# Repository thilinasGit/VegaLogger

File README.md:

# VegaLogger
This repo contains files that is used in telemetery data logger originally used in Vega ETX.

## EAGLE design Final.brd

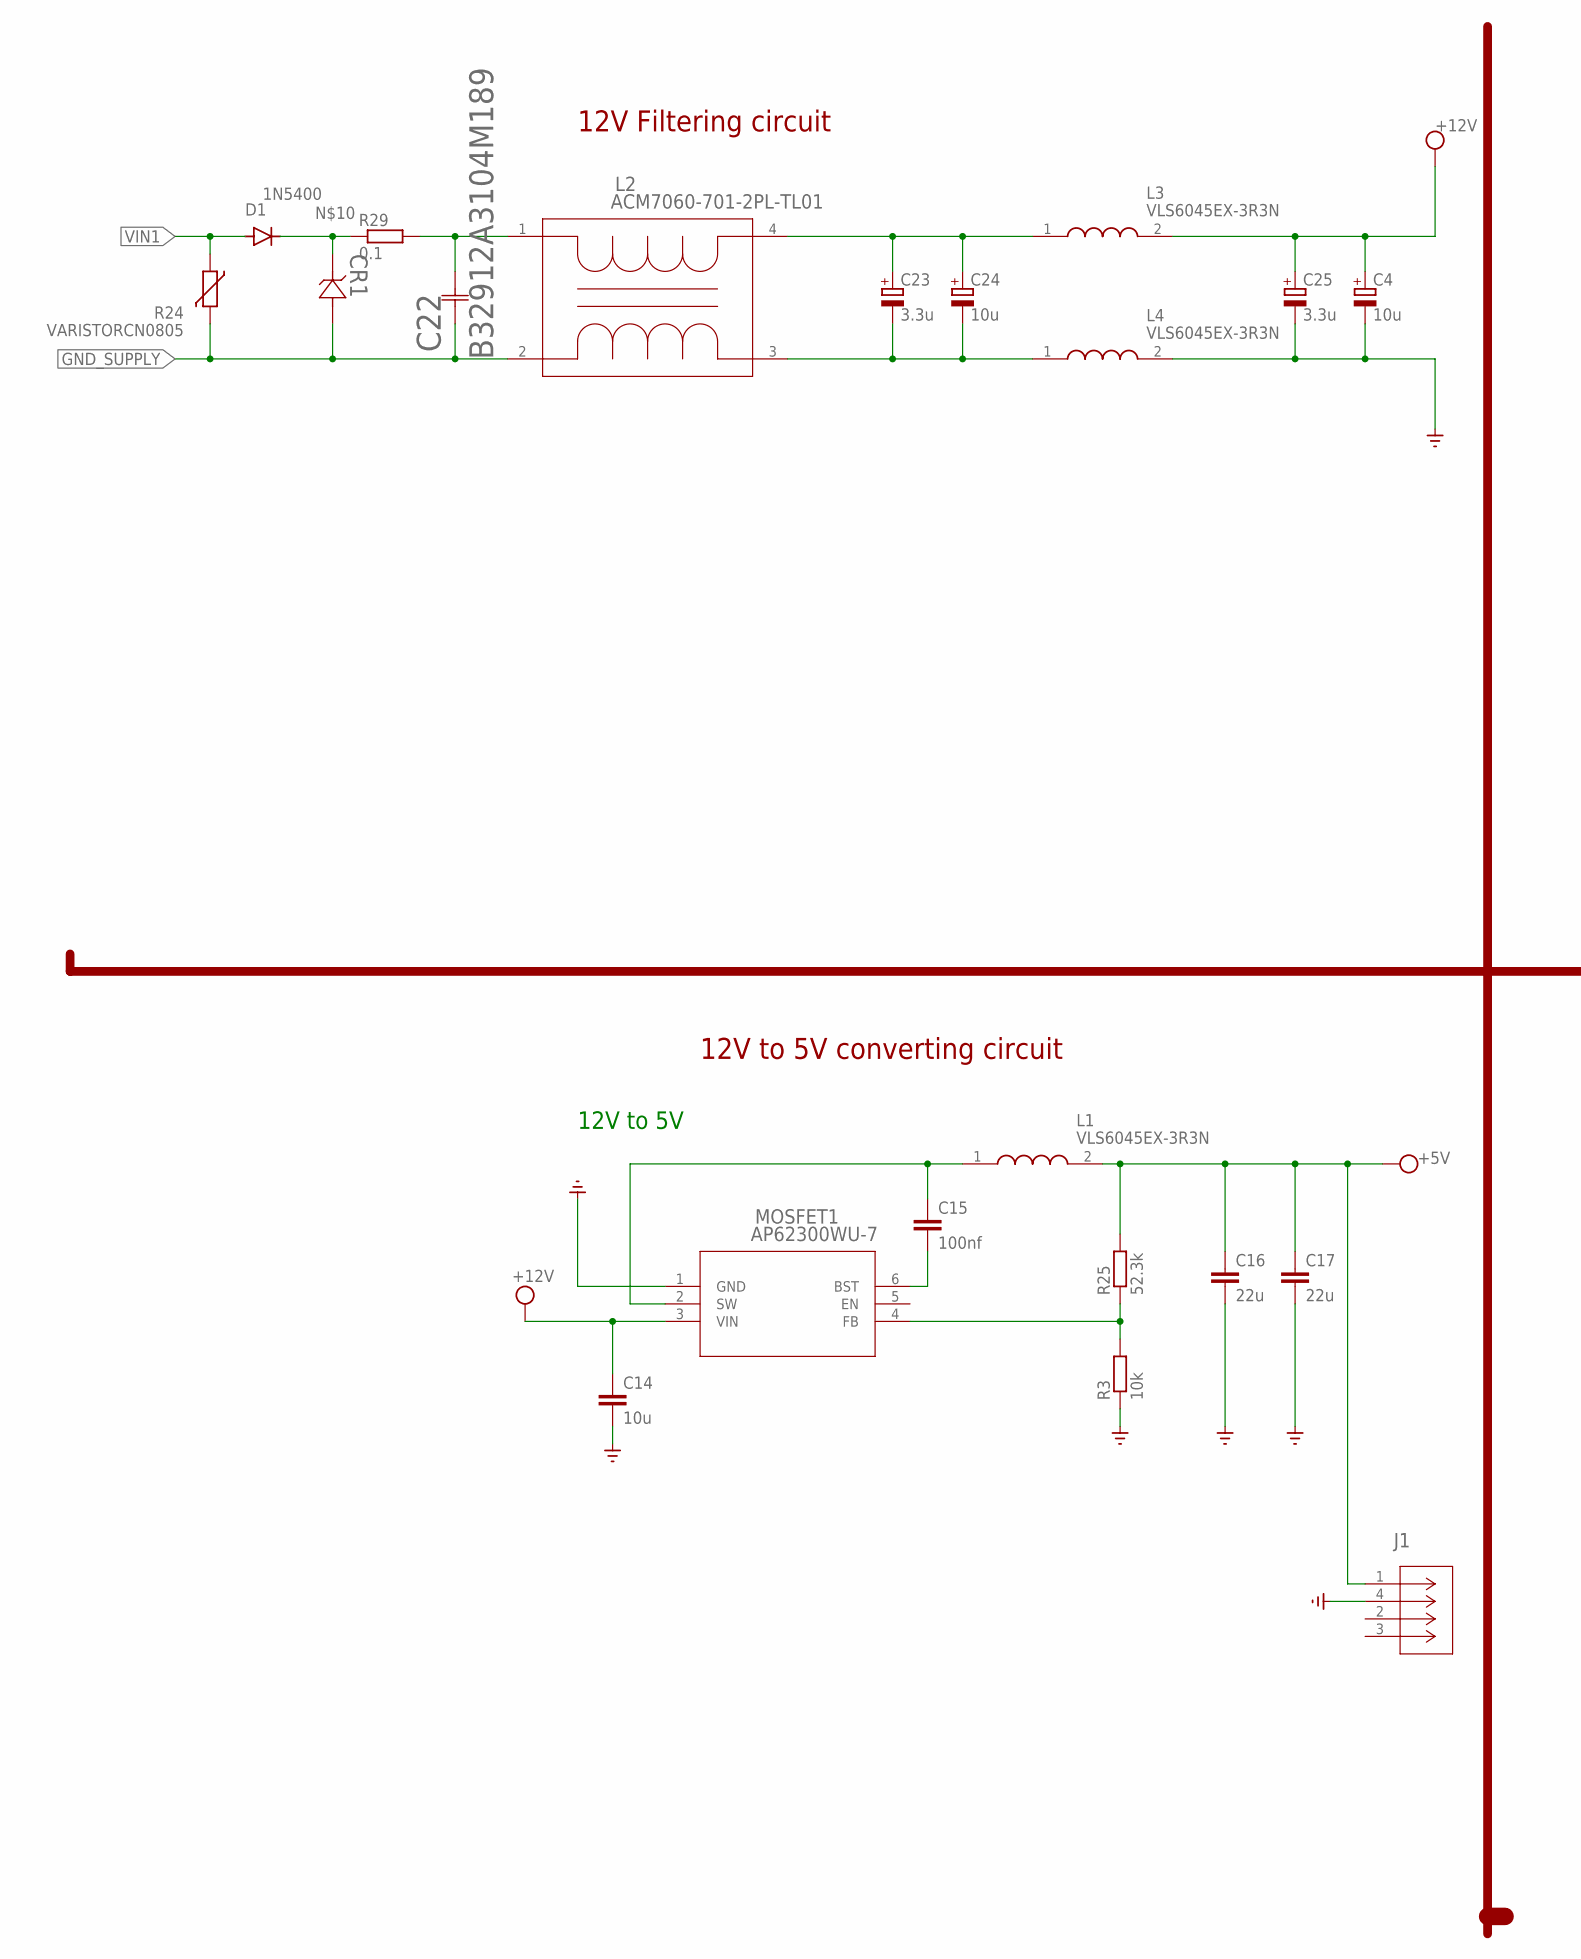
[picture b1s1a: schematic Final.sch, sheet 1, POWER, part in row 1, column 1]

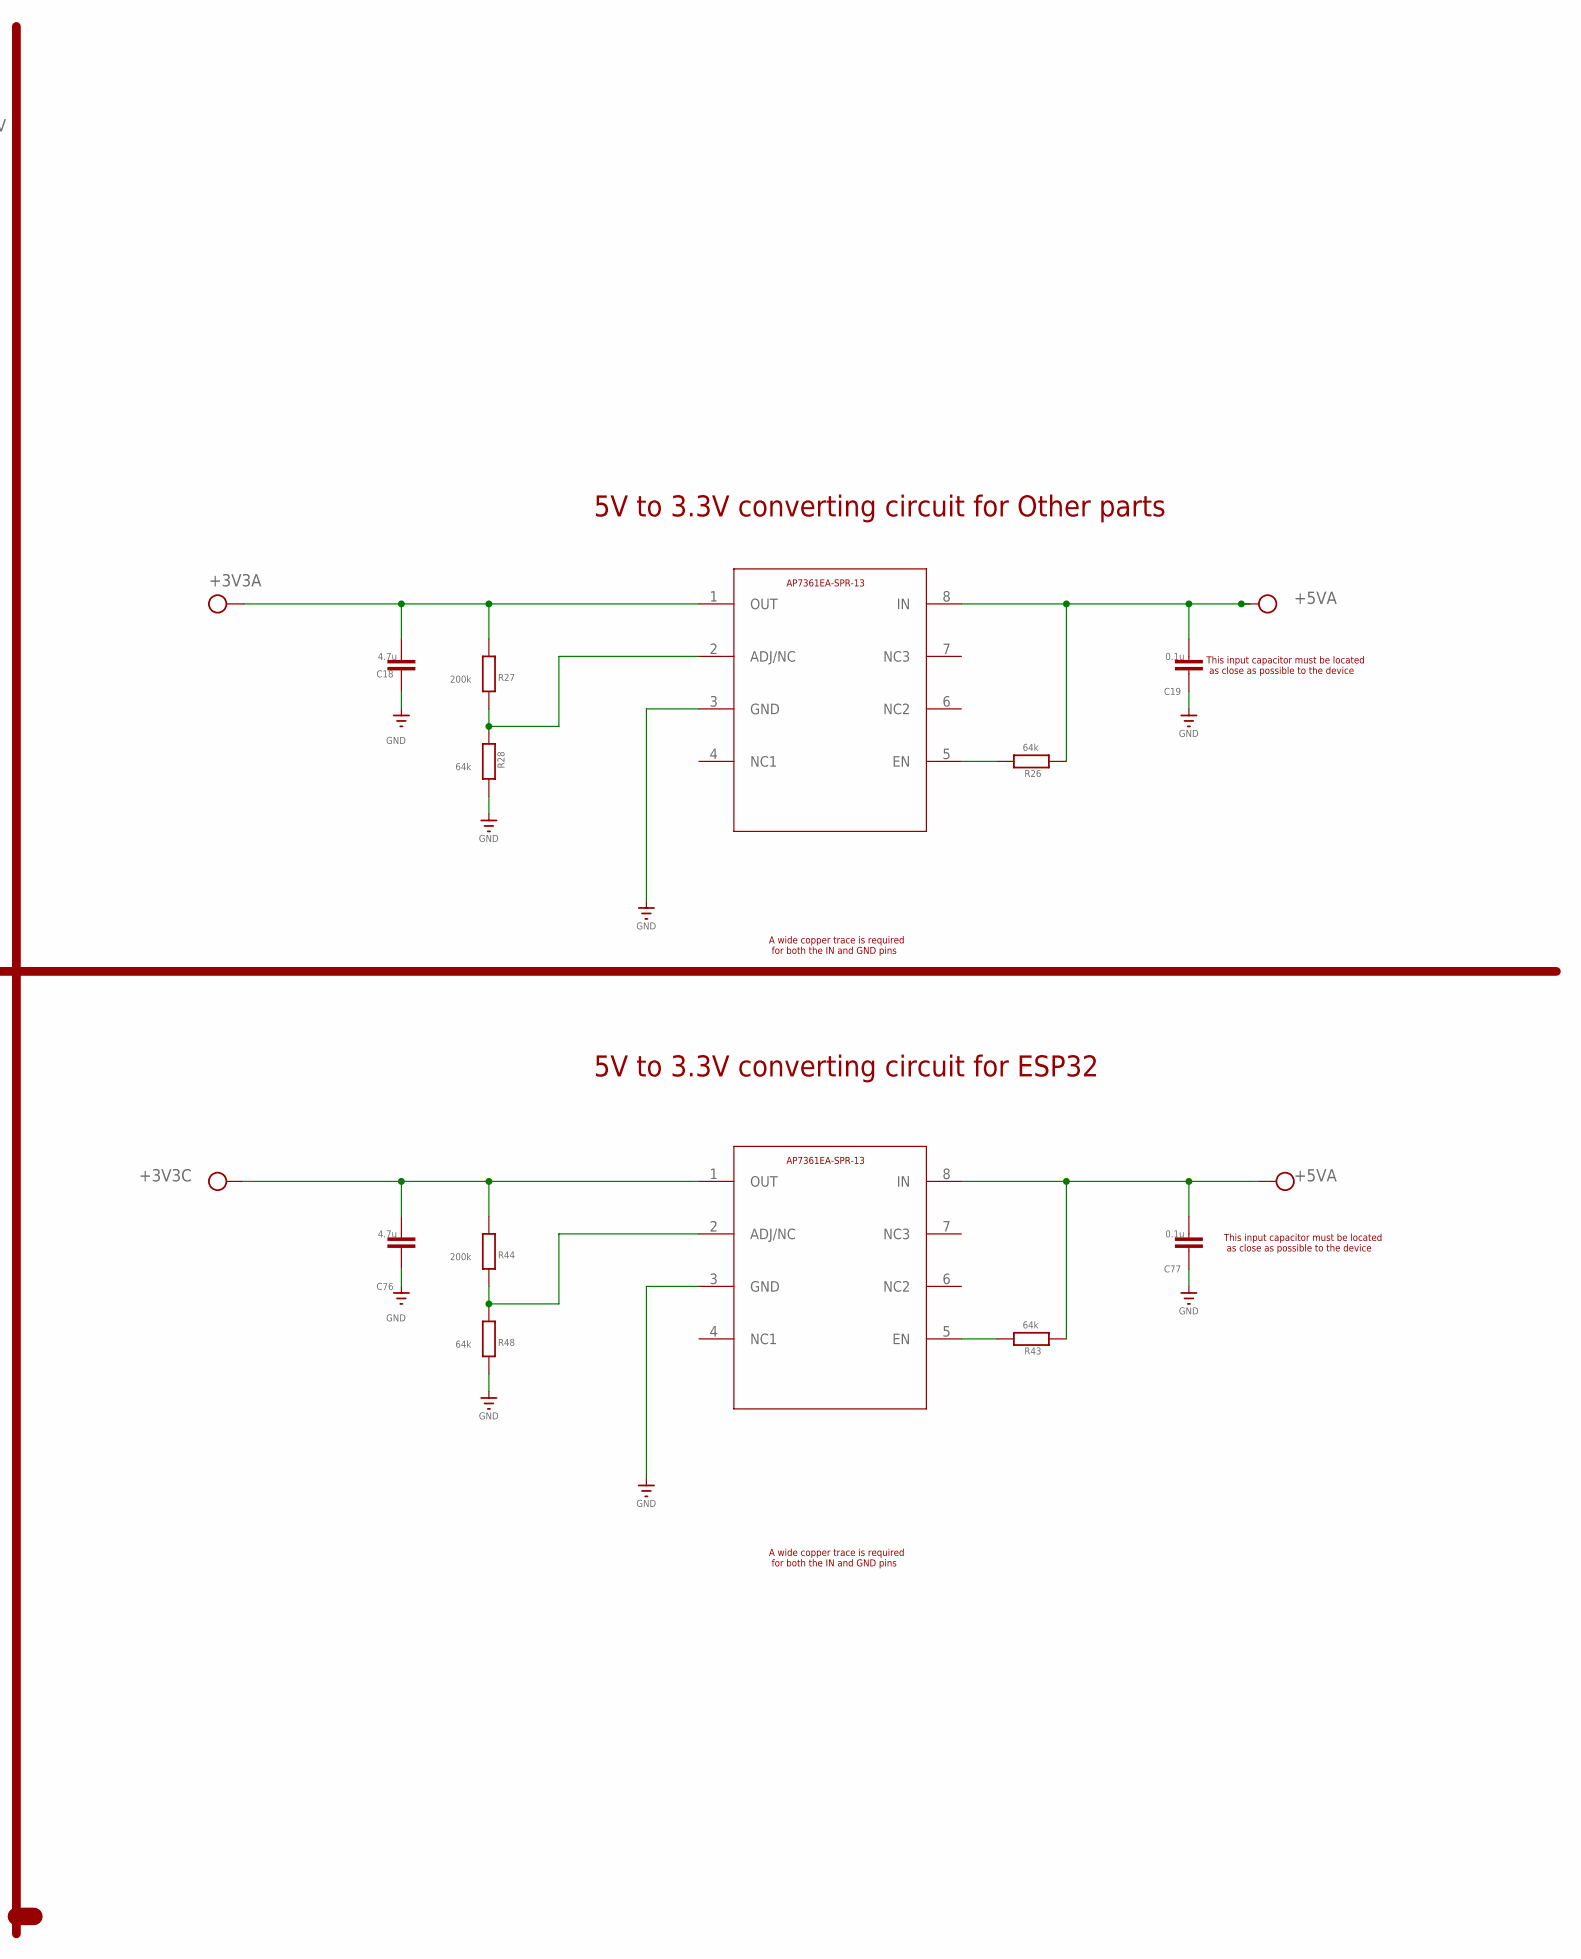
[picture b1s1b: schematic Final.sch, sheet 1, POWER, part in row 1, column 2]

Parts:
C4, C24: 10u; E2,5-5
C14: 10u; C0805
C15: 100nf; C0805
C16, C17: 22u; C0805
C18, C76: 4.7u; C0805
C19, C77: 0.1u; C0805
C22: B32912A3104M189; CAP_B32912A--15--7X12.5X18_TDK
C23, C25: 3.3u; E2,5-5
CR1: SM6T15ASMB_STM-L; SMB_STM-L
D1: 1N5400; DO201-15
J1: USB1130-15-A; CONN4_USB1130-15-A_GCT
L1, L3, L4: VLS6045EX-3R3N; VLS6045
L2: ACM7060-701-2PL-TL01; IND_ACM7060_TDK
MOSFET1: AP62300WU-7; TSOT26_DIO
R3: 10k; R0805
R24: VARISTORCN0805; CT/CN0805
R25: 52.3k; R0805
R26, R28, R43, R48: 64k; R0805
R27, R44: 200k; R0805
R29: 0.1; R1206
U$1, U$12: AP7361EASMD; AP7361EA

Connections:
+3V3A: C18.1, R27.1, U$1.1 (OUT); also elsewhere on the board
+3V3C: C76.1, R44.1, U$12.1 (OUT); also elsewhere on the board
+5V: C16.1, C17.1, J1.1, L1.2, R25.2; also elsewhere on the board
+5VA: C19.1, C77.1, R26.1, R43.1, U$1.8 (IN), U$12.8 (IN); also elsewhere on the board
+12V: C4.+, C14.1, C25.+, L3.2, MOSFET1.3 (VIN); also elsewhere on the board
GND: C4.-, C14.2, C16.2, C17.2, C18.2, C19.2, C25.-, C76.2, C77.2, J1.4, L4.2, MOSFET1.1 (GND), R3.1, R28.2, R48.2, U$1.3 (GND), U$12.3 (GND); also elsewhere on the board
GND_SUPPLY: C22.1, CR1.2, L2.2, R24.2; also elsewhere on the board
unnamed: CR1.1, D1.C, R29.1
unnamed: C23.+, C24.+, L2.4, L3.1
unnamed: C23.-, C24.-, L2.3, L4.1
unnamed: MOSFET1.4 (FB), R3.2, R25.1
unnamed: C15.1, L1.1, MOSFET1.2 (SW)
unnamed: C15.2, MOSFET1.6 (BST)
unnamed: R26.2, U$1.5 (EN)
unnamed: R27.2, R28.1, U$1.2 (ADJ/NC)
unnamed: R43.2, U$12.5 (EN)
unnamed: R44.2, R48.1, U$12.2 (ADJ/NC)
VIN: C22.2, L2.1, R29.2
VIN1: D1.A, R24.1; also elsewhere on the board

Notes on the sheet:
12V to 5V
This input capacitor must be located as close as possible to the device
A wide copper trace is required for both the IN and GND pins
12V Filtering circuit
12V to 5V converting circuit
5V to 3.3V converting circuit for ESP32
5V to 3.3V converting circuit for Other parts

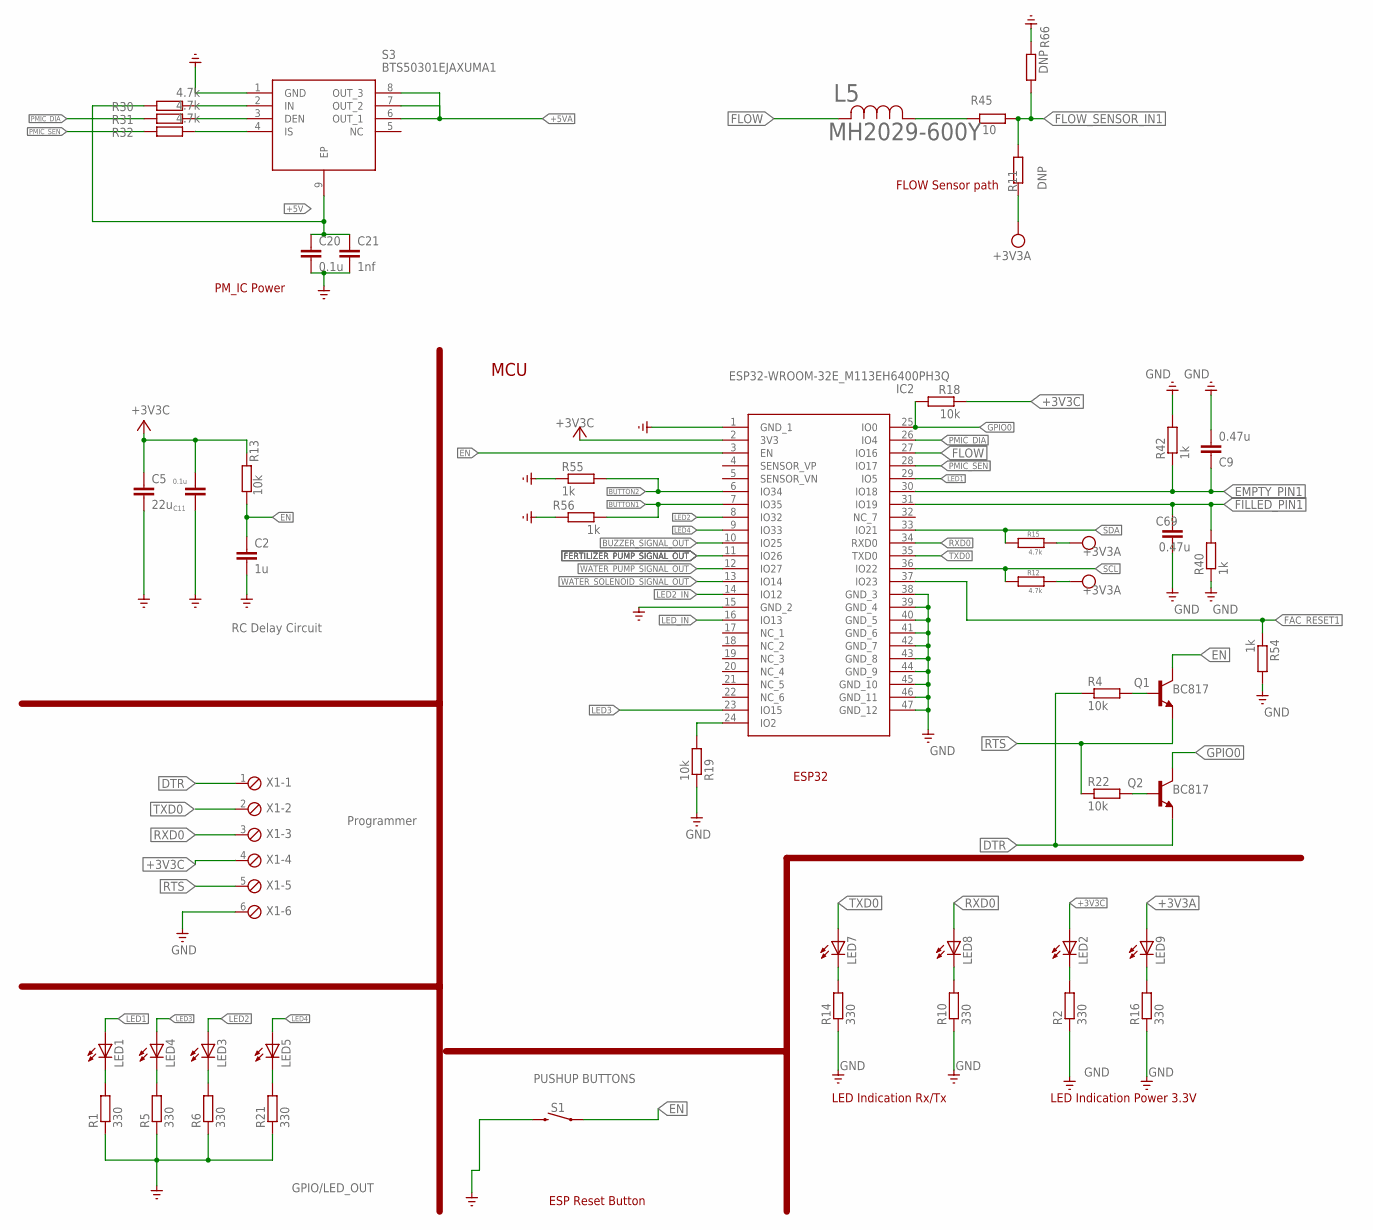
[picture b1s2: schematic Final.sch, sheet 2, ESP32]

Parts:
C2: 1u; C0805
C5: 22u; C0805
C9, C69: 0.47u; C0805
C11, C20: 0.1u; C0805
C21: 1nf; C0805
IC2: ESP32-WROOM-32E_M113EH6400PH3Q; ESP32WROOM32EM113EH6400PH3Q0
L5: MH2029-600Y; IND_BOURNS_MH2029
LED1, LED2, LED3, LED4, LED5, LED7, LED8, LED9: LEDCHIP-LED0603; CHIP-LED0603
Q1, Q2: BC817; SOT95P230X110-3N
R1, R2, R5, R6, R10, R14, R16, R21: 330; R0805
R4, R13, R18, R19, R22: 10k; R0805
R11, R66: DNP; R0805
R12, R15, R30, R31, R32: 4.7k; R0805
R40, R42, R54, R55, R56: 1k; R0805
R45: 10; R0805
S1: MOMENTARY-SWITCH-SPST-SMD-6.2MM-TALL; TACTILE_SWITCH_SMD_6.2MM_TALL
S3: BTS50301EJAXUMA1; SOIC127P600X170-9N
X1: MPT6; 6POL254

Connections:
+3V3A: LED9.A, R11.2, R12.1, R15.1; also elsewhere on the board
+3V3C: C5.1, C11.2, IC2.2 (3V3), LED2.A, R13.1, R18.1, X1.4; also elsewhere on the board
+5V: C20.1, C21.1, R30.1, S3.9 (EP); also elsewhere on the board
+5VA: S3.6 (OUT_1), S3.7 (OUT_2), S3.8 (OUT_3); also elsewhere on the board
BUTTON1: IC2.7 (IO35), R56.1; also elsewhere on the board
BUTTON2: IC2.6 (IO34), R55.2; also elsewhere on the board
BUZZER_SIGNAL_OUT: IC2.10 (IO25); also elsewhere on the board
DTR: Q2.2 (E), R4.1, X1.1
EMPTY_PIN1: C9.1, IC2.30 (IO18), R42.1; also elsewhere on the board
EN: C2.1, IC2.3 (EN), Q1.3 (C), R13.2, S1.A2 (1)
FAC_RESET1: IC2.37 (IO23), R54.1; also elsewhere on the board
FERTILIZER_PUMP_SIGNAL_OUT: IC2.11 (IO26); also elsewhere on the board
FILLED_PIN1: C69.1, IC2.31 (IO19), R40.2; also elsewhere on the board
FLOW: IC2.27 (IO16), L5.2
FLOW_SENSOR_IN1: R11.1, R45.1, R66.1; also elsewhere on the board
GND: C2.2, C5.2, C9.2, C11.1, C20.2, C21.2, C69.2, IC2.1 (GND_1), IC2.15 (GND_2), IC2.38 (GND_3), IC2.39 (GND_4), IC2.40 (GND_5), IC2.41 (GND_6), IC2.42 (GND_7), IC2.43 (GND_8), IC2.44 (GND_9), IC2.45 (GND_10), IC2.46 (GND_11), IC2.47 (GND_12), R1.1, R2.1, R5.1, R6.1, R10.1, R14.1, R16.1, R19.1, R21.1, R40.1, R42.2, R54.2, R55.1, R56.2, R66.2, S1.B2 (2), S3.1 (GND), X1.6; also elsewhere on the board
GPIO0: IC2.25 (IO0), Q2.3 (C), R18.2
LED1: IC2.29 (IO5), LED1.A
LED2: IC2.8 (IO32), LED3.A
LED2_IN: IC2.14 (IO12); also elsewhere on the board
LED3: IC2.23 (IO15), LED4.A
LED4: IC2.9 (IO33), LED5.A
LED_IN: IC2.16 (IO13); also elsewhere on the board
unnamed: LED2.C, R2.2
unnamed: LED1.C, R1.2
unnamed: L5.1, R45.2
unnamed: LED3.C, R6.2
unnamed: Q1.1 (B), R4.2
unnamed: IC2.24 (IO2), R19.2
unnamed: LED4.C, R5.2
unnamed: Q2.1 (B), R22.2
unnamed: LED5.C, R21.2
unnamed: R30.2, S3.2 (IN)
unnamed: R31.2, S3.3 (DEN)
unnamed: R32.2, S3.4 (IS)
unnamed: LED7.C, R14.2
unnamed: LED8.C, R10.2
unnamed: LED9.C, R16.2
PMIC_DIA: IC2.26 (IO4), R31.1
PMIC_SEN: IC2.28 (IO17), R32.1
RTS: Q1.2 (E), R22.1, X1.5
RXD0: IC2.34 (RXD0), LED8.A, X1.3; also elsewhere on the board
SCL: IC2.36 (IO22), R12.2; also elsewhere on the board
SDA: IC2.33 (IO21), R15.2; also elsewhere on the board
TXD0: IC2.35 (TXD0), LED7.A, X1.2; also elsewhere on the board
WATER_PUMP_SIGNAL_OUT: IC2.12 (IO27); also elsewhere on the board
WATER_SOLENOID_SIGNAL_OUT: IC2.13 (IO14); also elsewhere on the board

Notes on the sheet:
GPIO/LED_OUT
RC Delay Circuit
LED Indication Power 3.3V
PUSHUP BUTTONS
MCU
Programmer
LED Indication Rx/Tx
ESP Reset Button
ESP32
PM_IC Power
FLOW Sensor path

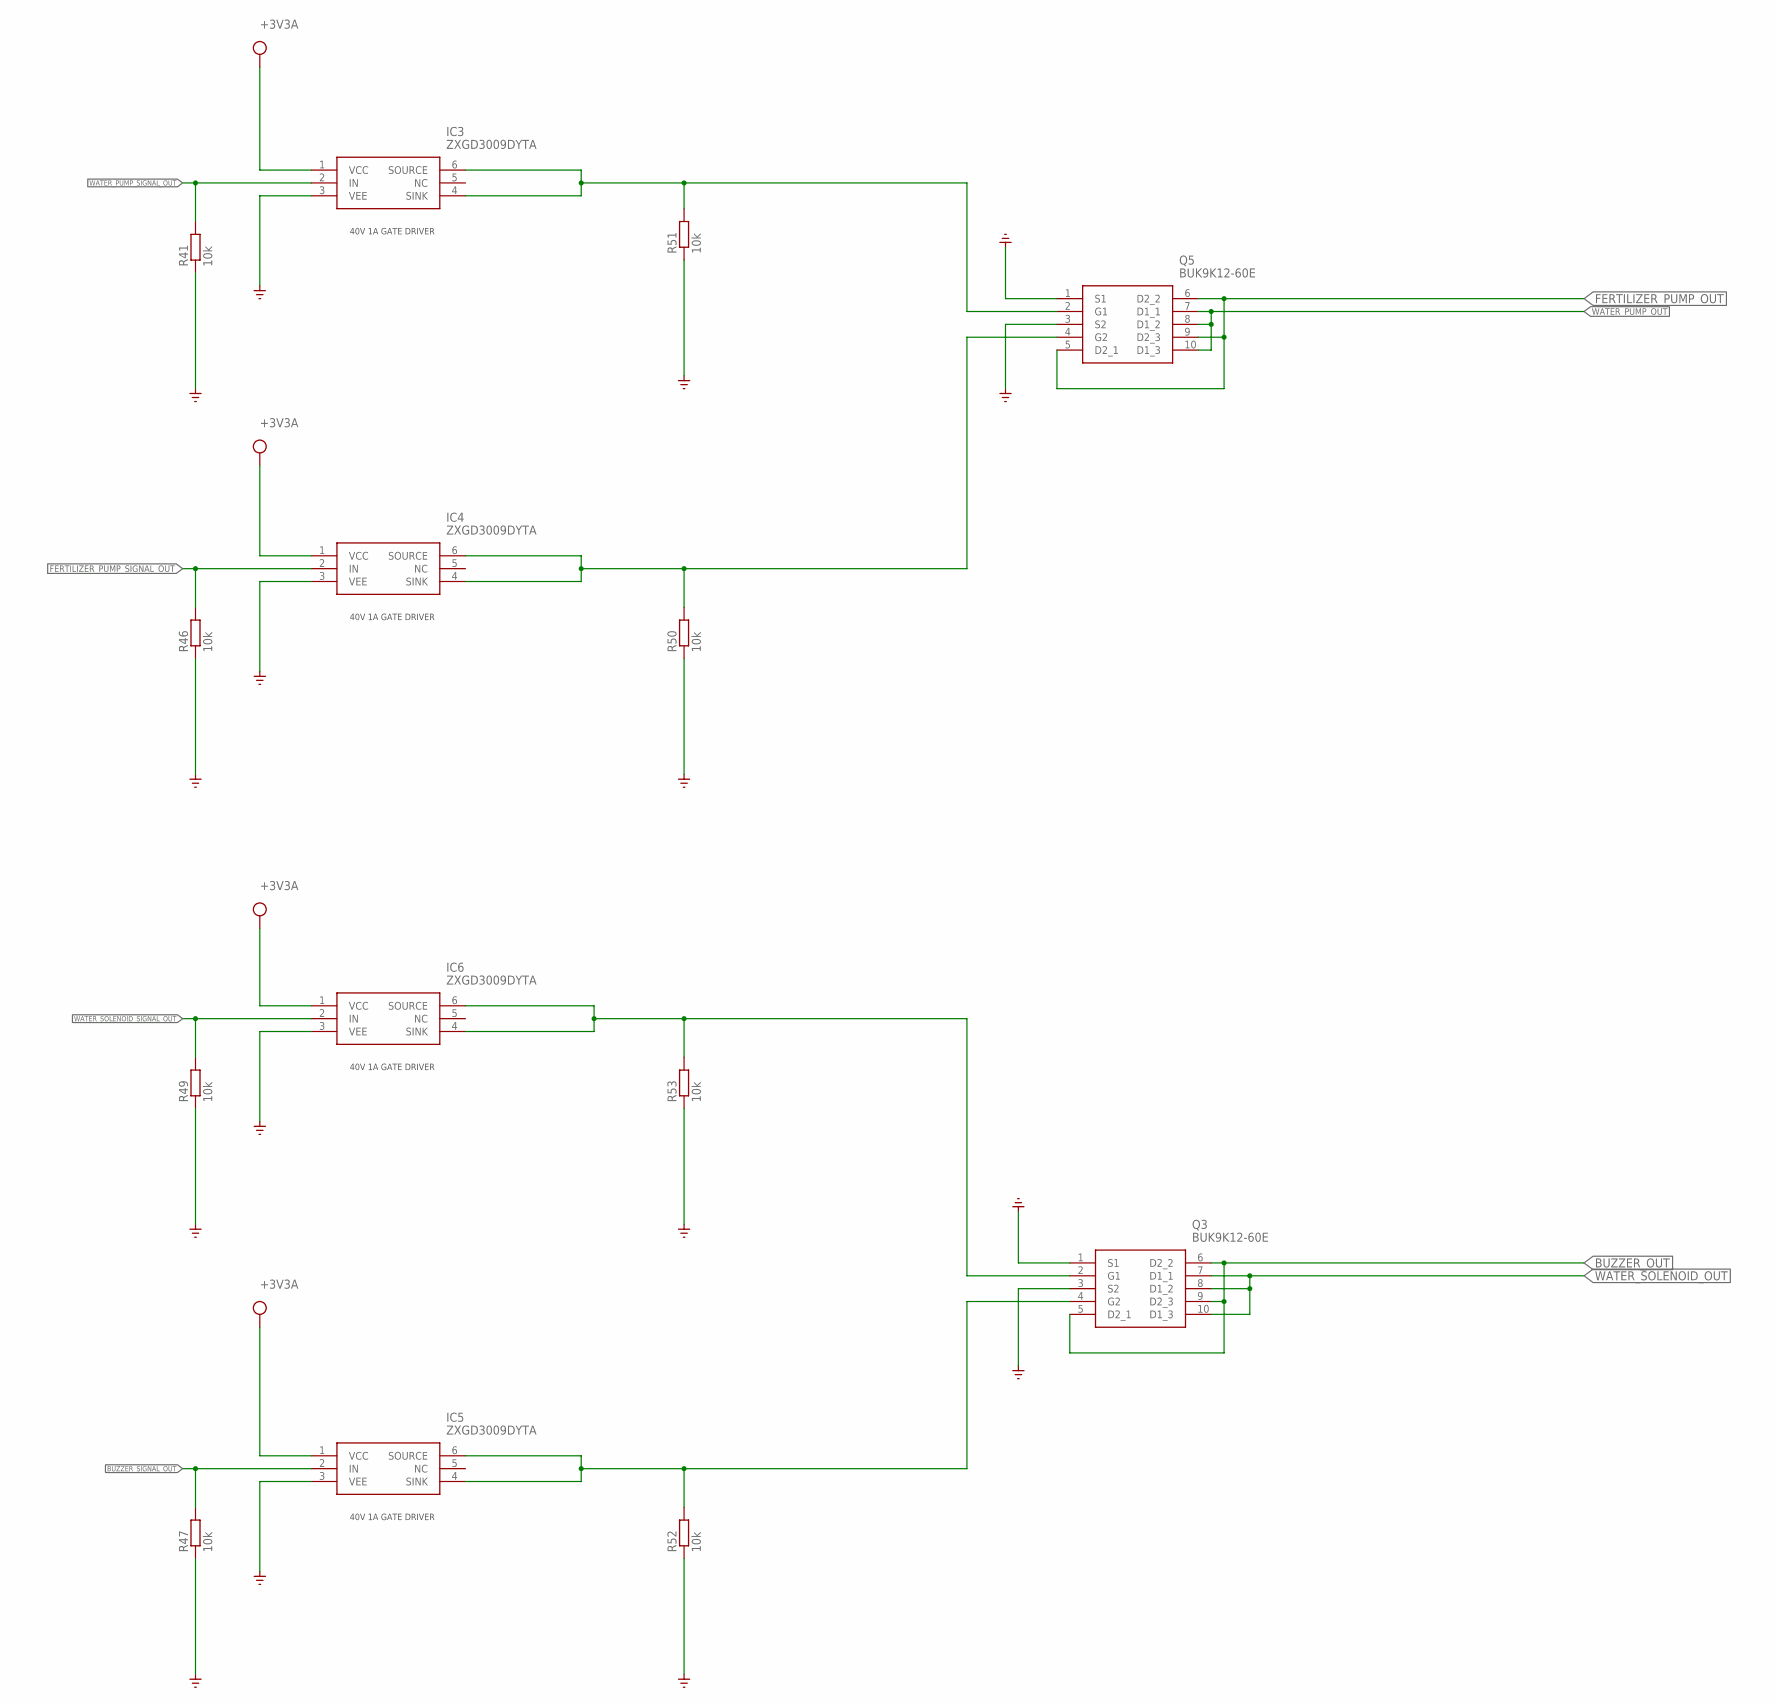
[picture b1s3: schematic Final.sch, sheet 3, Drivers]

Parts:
IC3, IC4, IC5, IC6: ZXGD3009DYTA; SOT65P210X110-6N
Q3, Q5: BUK9K12-60E
R41, R46, R47, R49, R50, R51, R52, R53: 10k; R0805

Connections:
+3V3A: IC3.1 (VCC), IC4.1 (VCC), IC5.1 (VCC), IC6.1 (VCC); also elsewhere on the board
BUZZER_OUT: Q3.5 (D2_1), Q3.6 (D2_2), Q3.9 (D2_3); also elsewhere on the board
BUZZER_SIGNAL_OUT: IC5.2 (IN), R47.2; also elsewhere on the board
FERTILIZER_PUMP_OUT: Q5.5 (D2_1), Q5.6 (D2_2), Q5.9 (D2_3); also elsewhere on the board
FERTILIZER_PUMP_SIGNAL_OUT: IC4.2 (IN), R46.2; also elsewhere on the board
GND: IC3.3 (VEE), IC4.3 (VEE), IC5.3 (VEE), IC6.3 (VEE), Q3.1 (S1), Q3.3 (S2), Q5.1 (S1), Q5.3 (S2), R41.1, R46.1, R47.1, R49.1, R50.1, R51.1, R52.1, R53.1; also elsewhere on the board
unnamed: IC3.4 (SINK), IC3.6 (SOURCE), Q5.2 (G1), R51.2
unnamed: IC4.4 (SINK), IC4.6 (SOURCE), Q5.4 (G2), R50.2
unnamed: IC5.4 (SINK), IC5.6 (SOURCE), Q3.4 (G2), R52.2
SOLENOID: IC6.4 (SINK), IC6.6 (SOURCE), Q3.2 (G1), R53.2
WATER_PUMP_OUT: Q5.7 (D1_1), Q5.8 (D1_2), Q5.10 (D1_3); also elsewhere on the board
WATER_PUMP_SIGNAL_OUT: IC3.2 (IN), R41.2; also elsewhere on the board
WATER_SOLENOID_OUT: Q3.7 (D1_1), Q3.8 (D1_2), Q3.10 (D1_3); also elsewhere on the board
WATER_SOLENOID_SIGNAL_OUT: IC6.2 (IN), R49.2; also elsewhere on the board

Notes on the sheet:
40V 1A GATE DRIVER

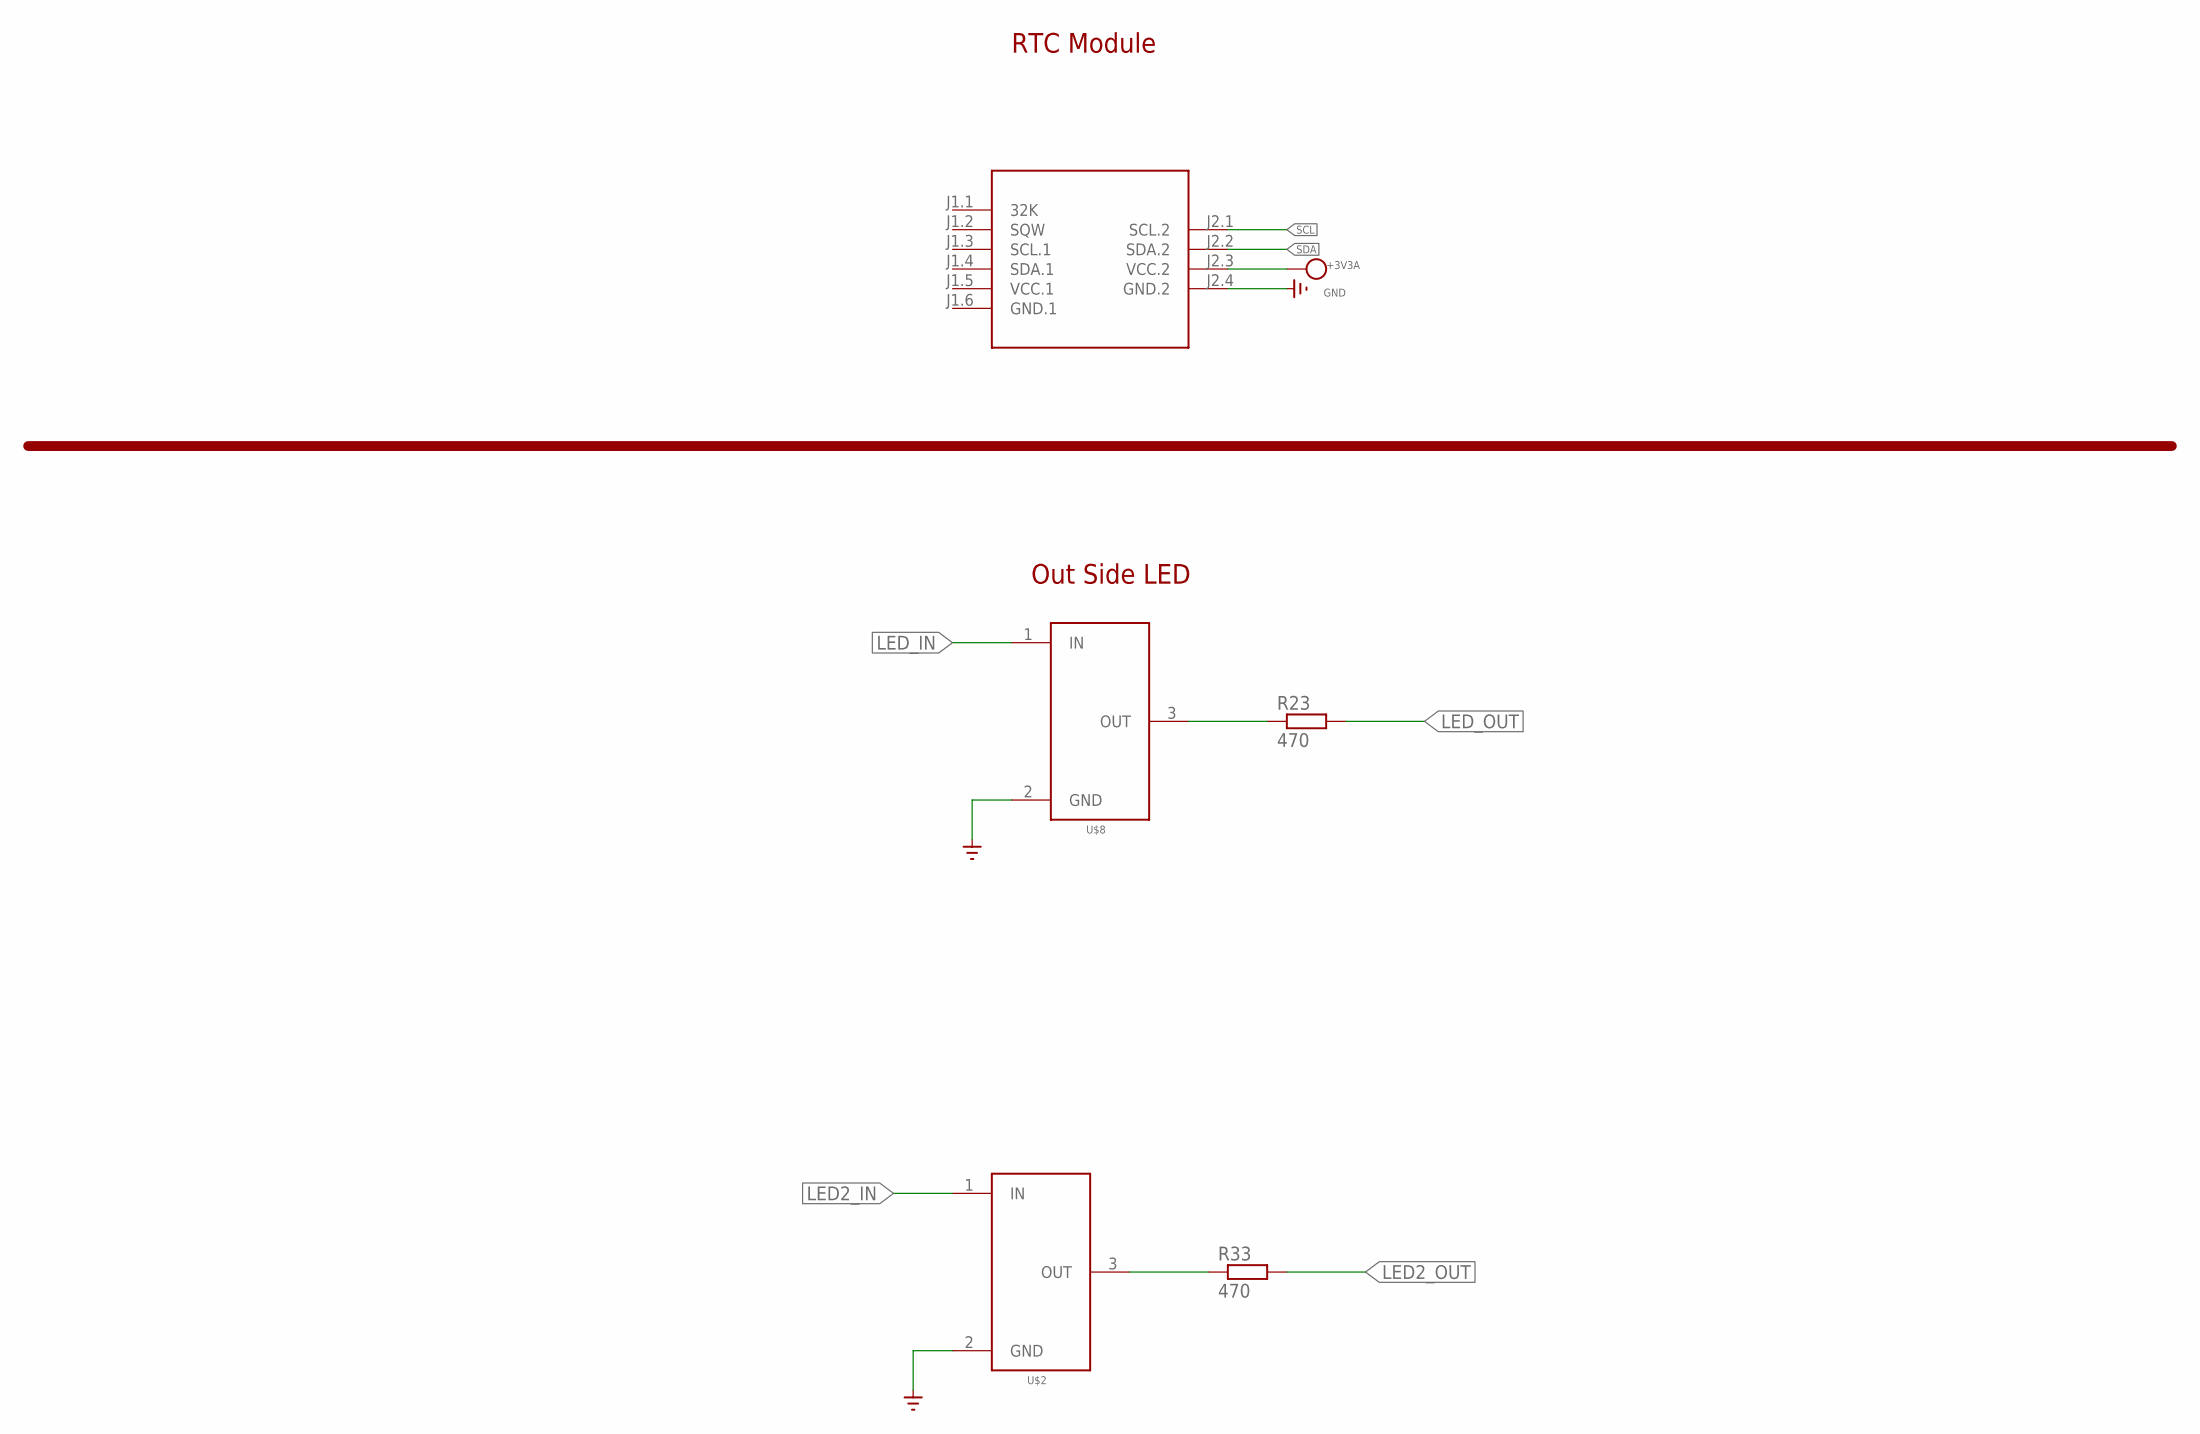
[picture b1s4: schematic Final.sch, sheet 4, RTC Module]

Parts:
R23, R33: 470; R0805
U$2, U$8: DDTD113ZC-7-F
U$3: RTC-DS3231-AT24C32

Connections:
+3V3A: U$3.J2.3 (VCC.2); also elsewhere on the board
GND: U$2.2 (GND), U$3.J2.4 (GND.2), U$8.2 (GND); also elsewhere on the board
GND.1: U$3.J1.6 (GND.1)
LED2_IN: U$2.1 (IN); also elsewhere on the board
LED2_OUT: R33.2; also elsewhere on the board
LED_IN: U$8.1 (IN); also elsewhere on the board
LED_OUT: R23.2; also elsewhere on the board
unnamed: R23.1, U$8.3 (OUT)
unnamed: R33.1, U$2.3 (OUT)
SCL: U$3.J2.1 (SCL.2); also elsewhere on the board
SDA: U$3.J2.2 (SDA.2); also elsewhere on the board
VCC.1: U$3.J1.5 (VCC.1)

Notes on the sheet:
RTC Module
Out Side LED

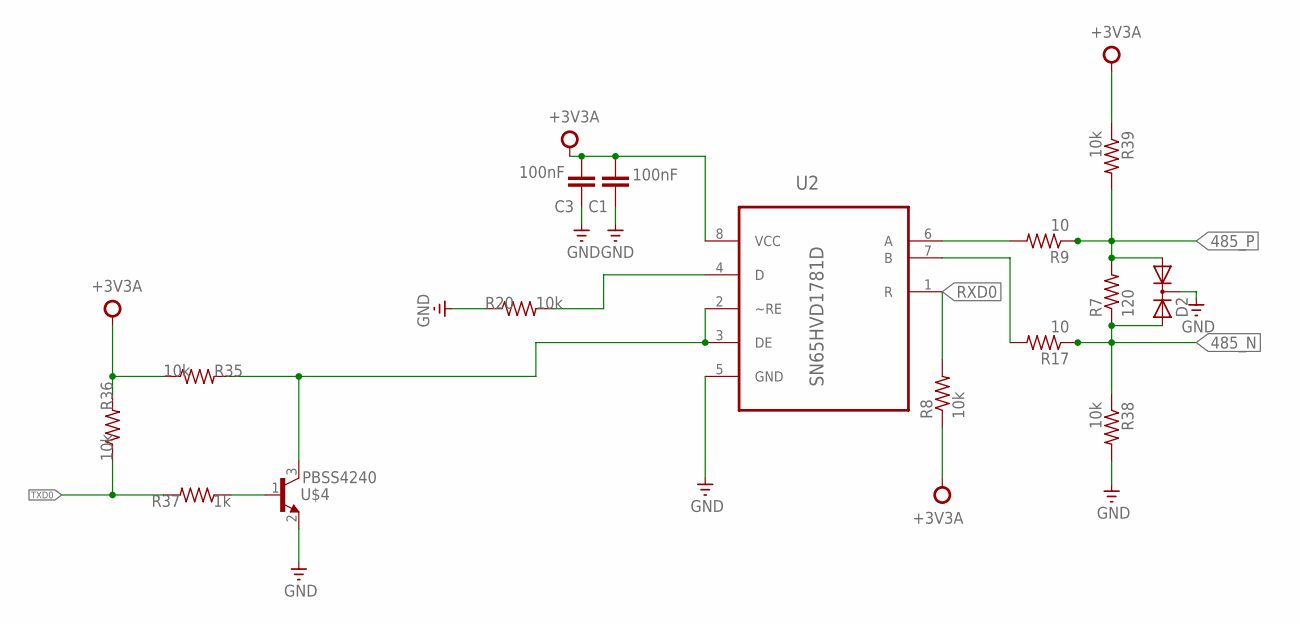
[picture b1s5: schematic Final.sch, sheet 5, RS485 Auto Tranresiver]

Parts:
C1, C3: 100nF; C0805
D2: DIODE-2AC|CASOT23; SOT23
R7: 120; R0805
R8, R20, R35, R36, R38, R39: 10k; R0805
R9, R17: 10; R0805
R37: 1k; R0805
U2: SN65HVD1781D; SOIC127P600X175-8N
U$4: PBSS4240; SOT23

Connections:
485_N: D2.2 (A2), R7.1, R17.1, R38.1; also elsewhere on the board
485_P: D2.1 (A1), R7.2, R9.1, R39.2; also elsewhere on the board
+3V3A: C1.2, C3.2, R8.1, R35.1, R36.2, R39.1, U2.8 (VCC); also elsewhere on the board
GND: C1.1, C3.1, D2.3 (C), R20.1, R38.2, U2.5 (GND), U$4.2 (E); also elsewhere on the board
unnamed: R9.2, U2.6 (A)
unnamed: R17.2, U2.7 (B)
unnamed: R20.2, U2.4 (D)
unnamed: R35.2, U2.2 (~RE), U2.3 (DE), U$4.3 (C)
unnamed: R37.1, U$4.1 (B)
RXD0: R8.2, U2.1 (R); also elsewhere on the board
TXD0: R36.1, R37.2; also elsewhere on the board

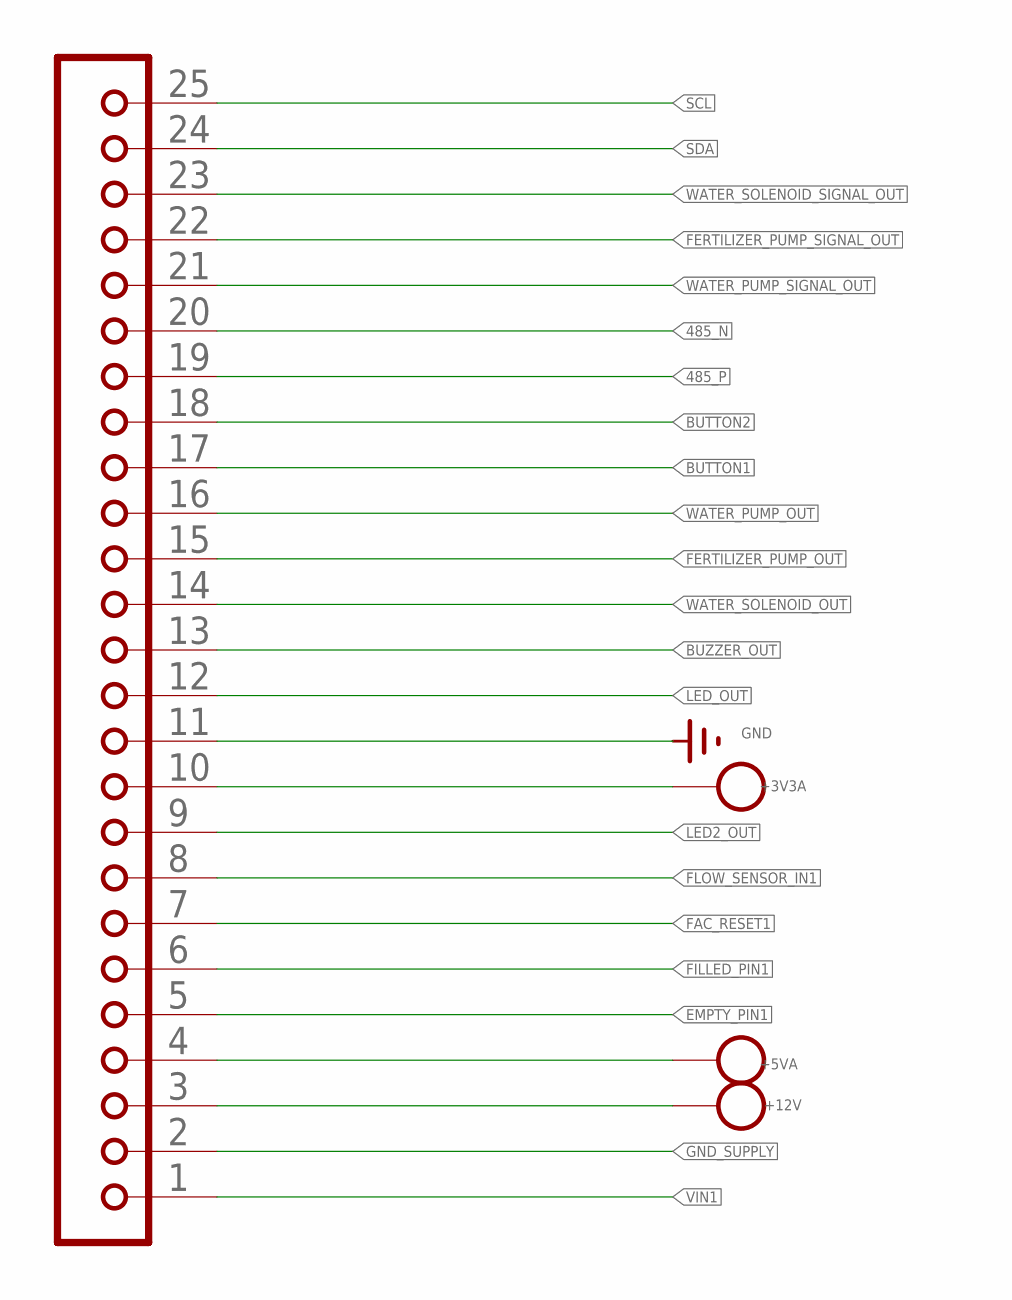
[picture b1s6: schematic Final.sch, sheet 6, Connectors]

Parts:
J2: JBK20L

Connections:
485_N: J2.20; also elsewhere on the board
485_P: J2.19; also elsewhere on the board
+3V3A: J2.10; also elsewhere on the board
+5VA: J2.4; also elsewhere on the board
+12V: J2.3; also elsewhere on the board
BUTTON1: J2.17; also elsewhere on the board
BUTTON2: J2.18; also elsewhere on the board
BUZZER_OUT: J2.13; also elsewhere on the board
EMPTY_PIN1: J2.5; also elsewhere on the board
FAC_RESET1: J2.7; also elsewhere on the board
FERTILIZER_PUMP_OUT: J2.15; also elsewhere on the board
FERTILIZER_PUMP_SIGNAL_OUT: J2.22; also elsewhere on the board
FILLED_PIN1: J2.6; also elsewhere on the board
FLOW_SENSOR_IN1: J2.8; also elsewhere on the board
GND: J2.11; also elsewhere on the board
GND_SUPPLY: J2.2; also elsewhere on the board
LED2_OUT: J2.9; also elsewhere on the board
LED_OUT: J2.12; also elsewhere on the board
SCL: J2.25; also elsewhere on the board
SDA: J2.24; also elsewhere on the board
VIN1: J2.1; also elsewhere on the board
WATER_PUMP_OUT: J2.16; also elsewhere on the board
WATER_PUMP_SIGNAL_OUT: J2.21; also elsewhere on the board
WATER_SOLENOID_OUT: J2.14; also elsewhere on the board
WATER_SOLENOID_SIGNAL_OUT: J2.23; also elsewhere on the board

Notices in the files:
parts and their libraries:
SparkFun-Switches: Licensing: Creative Commons ShareAlike 4.0 International - https://creativecommons.org/licenses/by-sa/4.0
diy-modules: Released under the Creative Commons Attribution 4.0 International License: http://creativecommons.org/licenses/by/4.0
